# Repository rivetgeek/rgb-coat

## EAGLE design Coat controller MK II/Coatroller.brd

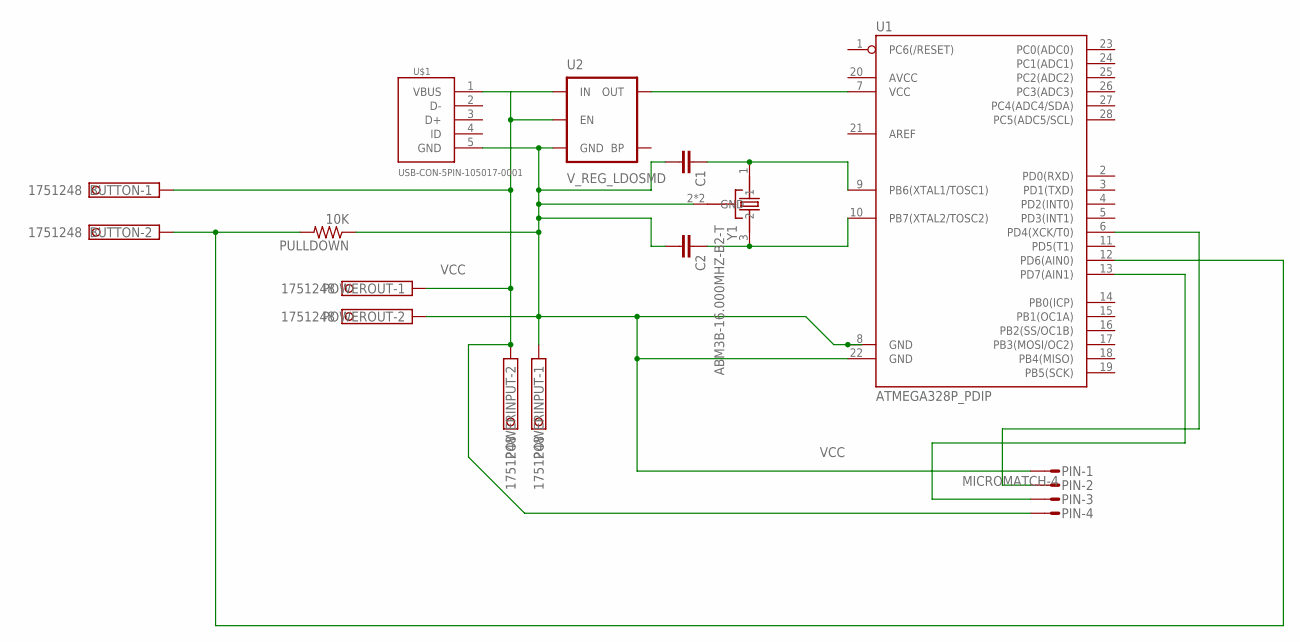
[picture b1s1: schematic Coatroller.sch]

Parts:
BUTTON: 1751248
C1, C2: 2.2UF50V10%(1206); 1206-CAP
PIN: MICROMATCH-4
POWERINPUT: 1751248
POWEROUT: 1751248
PULLDOWN: 10K; 0603-RES
U1: ATMEGA328P_PDIP; DIL28-3
U2: V_REG_LDOSMD; SOT23-5
U$1: USB-CON-5PIN-105017-0001; USB-MICRO-MOLEX-105017-0001
Y1: ABM3B-16.000MHZ-B2-T; OSCSC500X320X110-4N

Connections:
5V: U1.7 (VCC), U2.5 (OUT)
BUTTONPIN: BUTTON.2, PULLDOWN.2, U1.12 (PD6(AIN0))
CLOCK: PIN.2, U1.6 (PD4(XCK/T0))
DATA: PIN.3, U1.13 (PD7(AIN1))
GROUND: C1.2, C2.2, PIN.1, POWERINPUT.1, POWEROUT.2, PULLDOWN.1, U1.8 (GND), U1.22 (GND), U2.2 (GND), U$1.5 (GND), Y1.2 (GND), Y1.4 (GND)
unnamed: C1.1, U1.9 (PB6(XTAL1/TOSC1)), Y1.1
unnamed: C2.1, U1.10 (PB7(XTAL2/TOSC2)), Y1.3 (2)
VCC: BUTTON.1, PIN.4, POWERINPUT.2, POWEROUT.1, U2.1 (IN), U2.3 (EN), U$1.1 (VBUS)

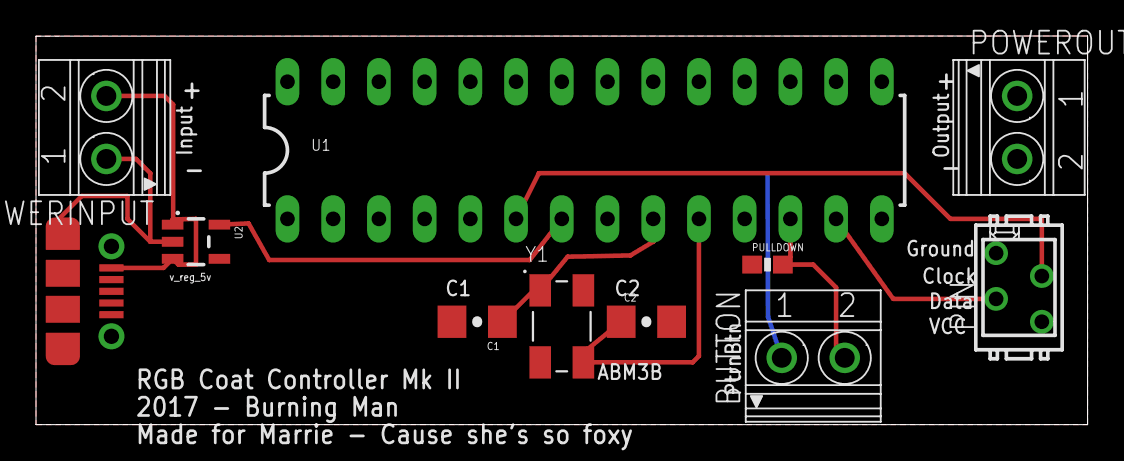
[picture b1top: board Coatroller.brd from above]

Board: 2 copper layers, 58.4 x 21.6 mm, 11 parts (0 on the bottom side), 8 nets.

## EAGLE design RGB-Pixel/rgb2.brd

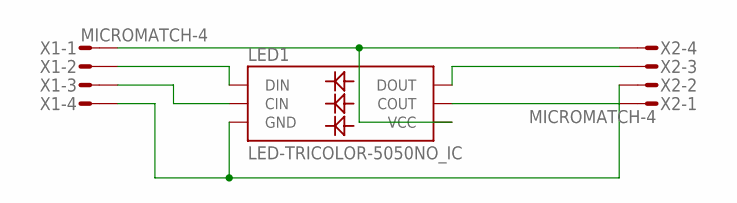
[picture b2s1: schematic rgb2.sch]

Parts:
LED1: LED-TRICOLOR-5050NO_IC; LED-TRICOLOR-5050
X1, X2: MICROMATCH-4

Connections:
unnamed: LED1.4 (VCC), X1.1, X2.4
unnamed: LED1.1 (DIN), X1.2
unnamed: LED1.2 (CIN), X1.3
unnamed: LED1.3 (GND), X1.4, X2.1
unnamed: LED1.5 (COUT), X2.2
unnamed: LED1.6 (DOUT), X2.3

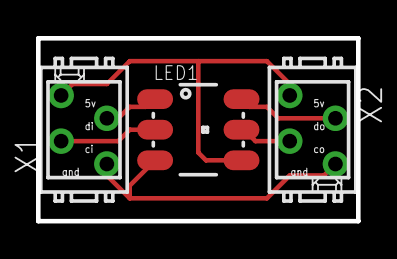
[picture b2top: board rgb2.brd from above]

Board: 2 copper layers, 17.8 x 10.2 mm, 3 parts (0 on the bottom side), 6 nets.

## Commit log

2016-02-27 two leds working, one at a time
2016-02-27 testing sshe key
2016-03-07 Fixed timing issues
2016-03-07 janky fix for duplicate pixels
2016-07-30 FIxed everything this is working now
2017-05-02 Added rgb-coat circuit files
2017-05-03 added reversed files
2017-05-22 Final board before fab house. Added mounting holes.
2017-05-31 added stencil file and gerbers
2017-07-10 basic working coat. a few overwrite bugs
2017-07-10 Fixed pixel overwrite bug
2017-07-20 new coat controller started
2017-07-20 added more parts
2017-07-20 finished placing and routing
2017-07-21 Fixed crystal and caps
2017-07-22 Fixed usb direction and fixed some routing
2017-07-22 rotated micromatch to proper direction and rerouted. Fixed a few crossed routes
2017-07-24 expect this is production level
2017-07-24 final version for 2017. Added breakouts for power and rx/tx
2017-08-05 last commit for MKII
2017-08-19 Made matrices for both armsand increased num_leds to proper size
2017-08-22 flower working. bug in button and pulse
2017-08-22 fixed bug where flower wasnt respecting the max pixels. pulse is still weird
2017-08-22 maybe fixed the flower bug. who knows
2017-08-22 fixed a few bugs
2017-08-22 found a few bugs and of by one errors
2017-08-23 Flower pattern is working. increased max pixels to 60. Pulse does not move from starting position
2017-08-23 pulse is mostly working. weird bug in the left arm though, its stopping halfway up. need to make the transition between rows smoother and add trails behind it. Perhaps some dithering on the come up
2017-08-24 fixed huge num_pixels bug and arm matrices. flower works 100% and pulse is working but rough
2017-08-26 Final playa-ready version of the Impossible Coat.
2017-08-26 slowed down the flower pattern and reduced the number of pixels active to reduce flickering

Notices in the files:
parts and their libraries:
SparkFun-DigitalIC: Licensing: Creative Commons ShareAlike 4.0 International - https://creativecommons.org/licenses/by-sa/4.0
